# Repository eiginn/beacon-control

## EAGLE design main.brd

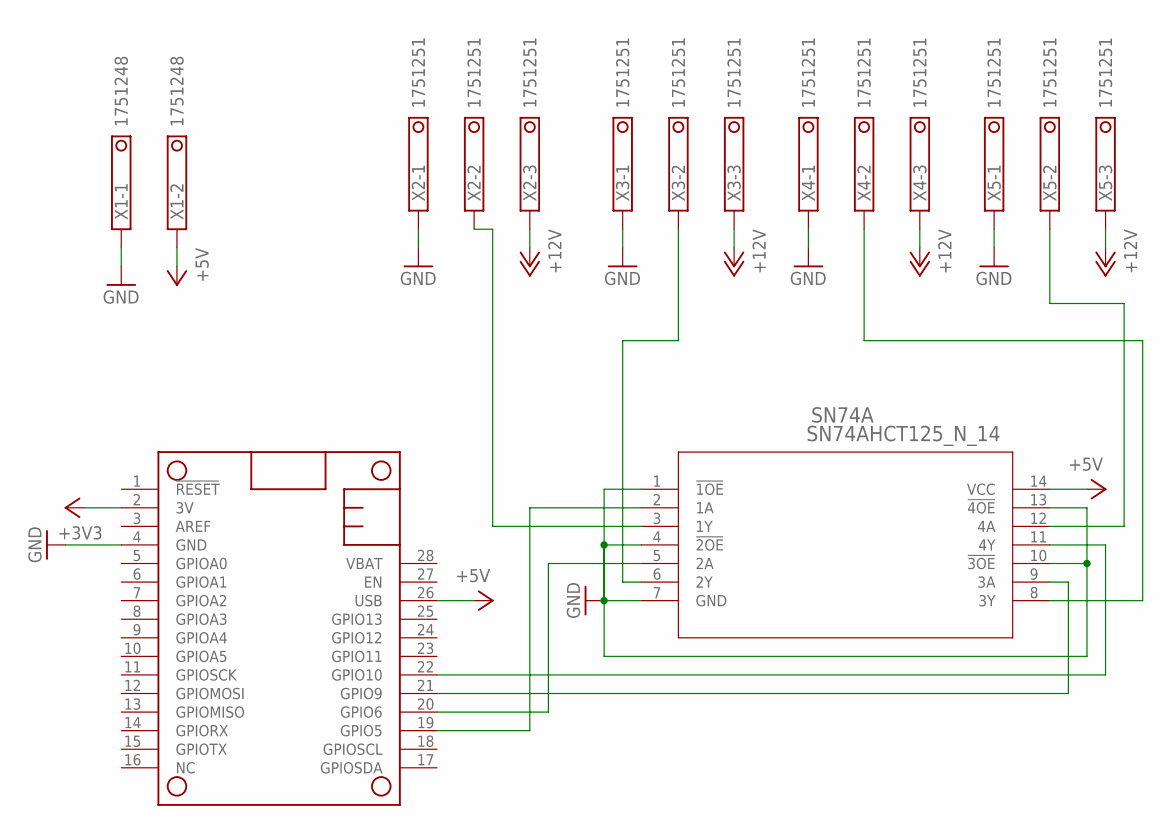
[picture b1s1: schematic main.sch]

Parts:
MS1: FEATHERWING_NODIM; FEATHERWING_DIM
SN74A: SN74AHCT125_N_14; N14
X1: 1751248
X2, X3, X4, X5: 1751251

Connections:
+3V3: MS1.2 (3V)
+5V: MS1.26 (USB), SN74A.14 (VCC), X1.2
+12V: X2.3, X3.3, X4.3, X5.3
GND: MS1.4 (GND), SN74A.1 (!1OE), SN74A.4 (!2OE), SN74A.7 (GND), SN74A.10 (!3OE), SN74A.13 (!4OE), X1.1, X2.1, X3.1, X4.1, X5.1
HDATA1: SN74A.3 (1Y), X2.2
HDATA2: SN74A.6 (2Y), X3.2
HDATA3: SN74A.8 (3Y), X4.2
HDATA4: SN74A.12 (4A), X5.2
LDATA1: MS1.19 (GPIO5), SN74A.2 (1A)
LDATA2: MS1.20 (GPIO6), SN74A.5 (2A)
LDATA3: MS1.21 (GPIO9), SN74A.9 (3A)
LDATA4: MS1.22 (GPIO10), SN74A.11 (4Y)

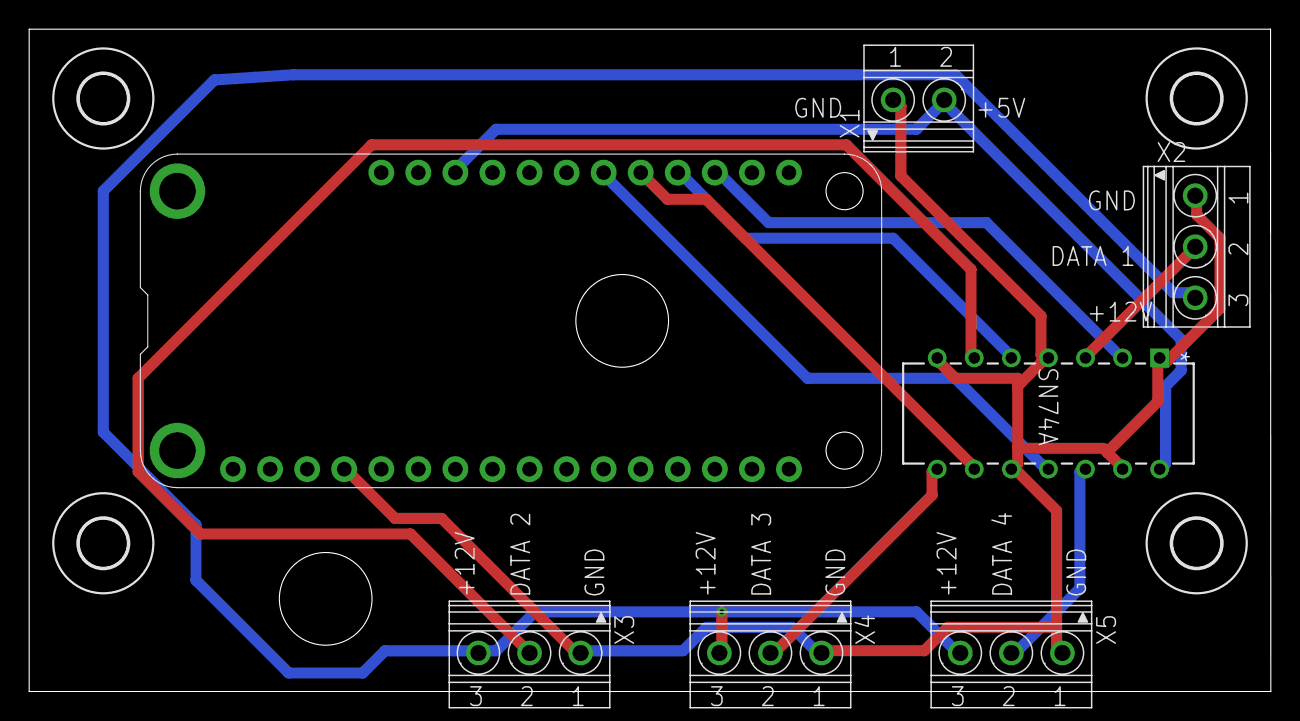
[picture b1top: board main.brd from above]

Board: 2 copper layers, 85.1 x 45.4 mm, 11 parts (0 on the bottom side), 11 nets.

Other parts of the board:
U$2, U$3, U$4, U$5: 3,3
